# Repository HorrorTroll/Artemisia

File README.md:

# Artemisia
A Pro Micro using ArteryTek AT32F415 MCU

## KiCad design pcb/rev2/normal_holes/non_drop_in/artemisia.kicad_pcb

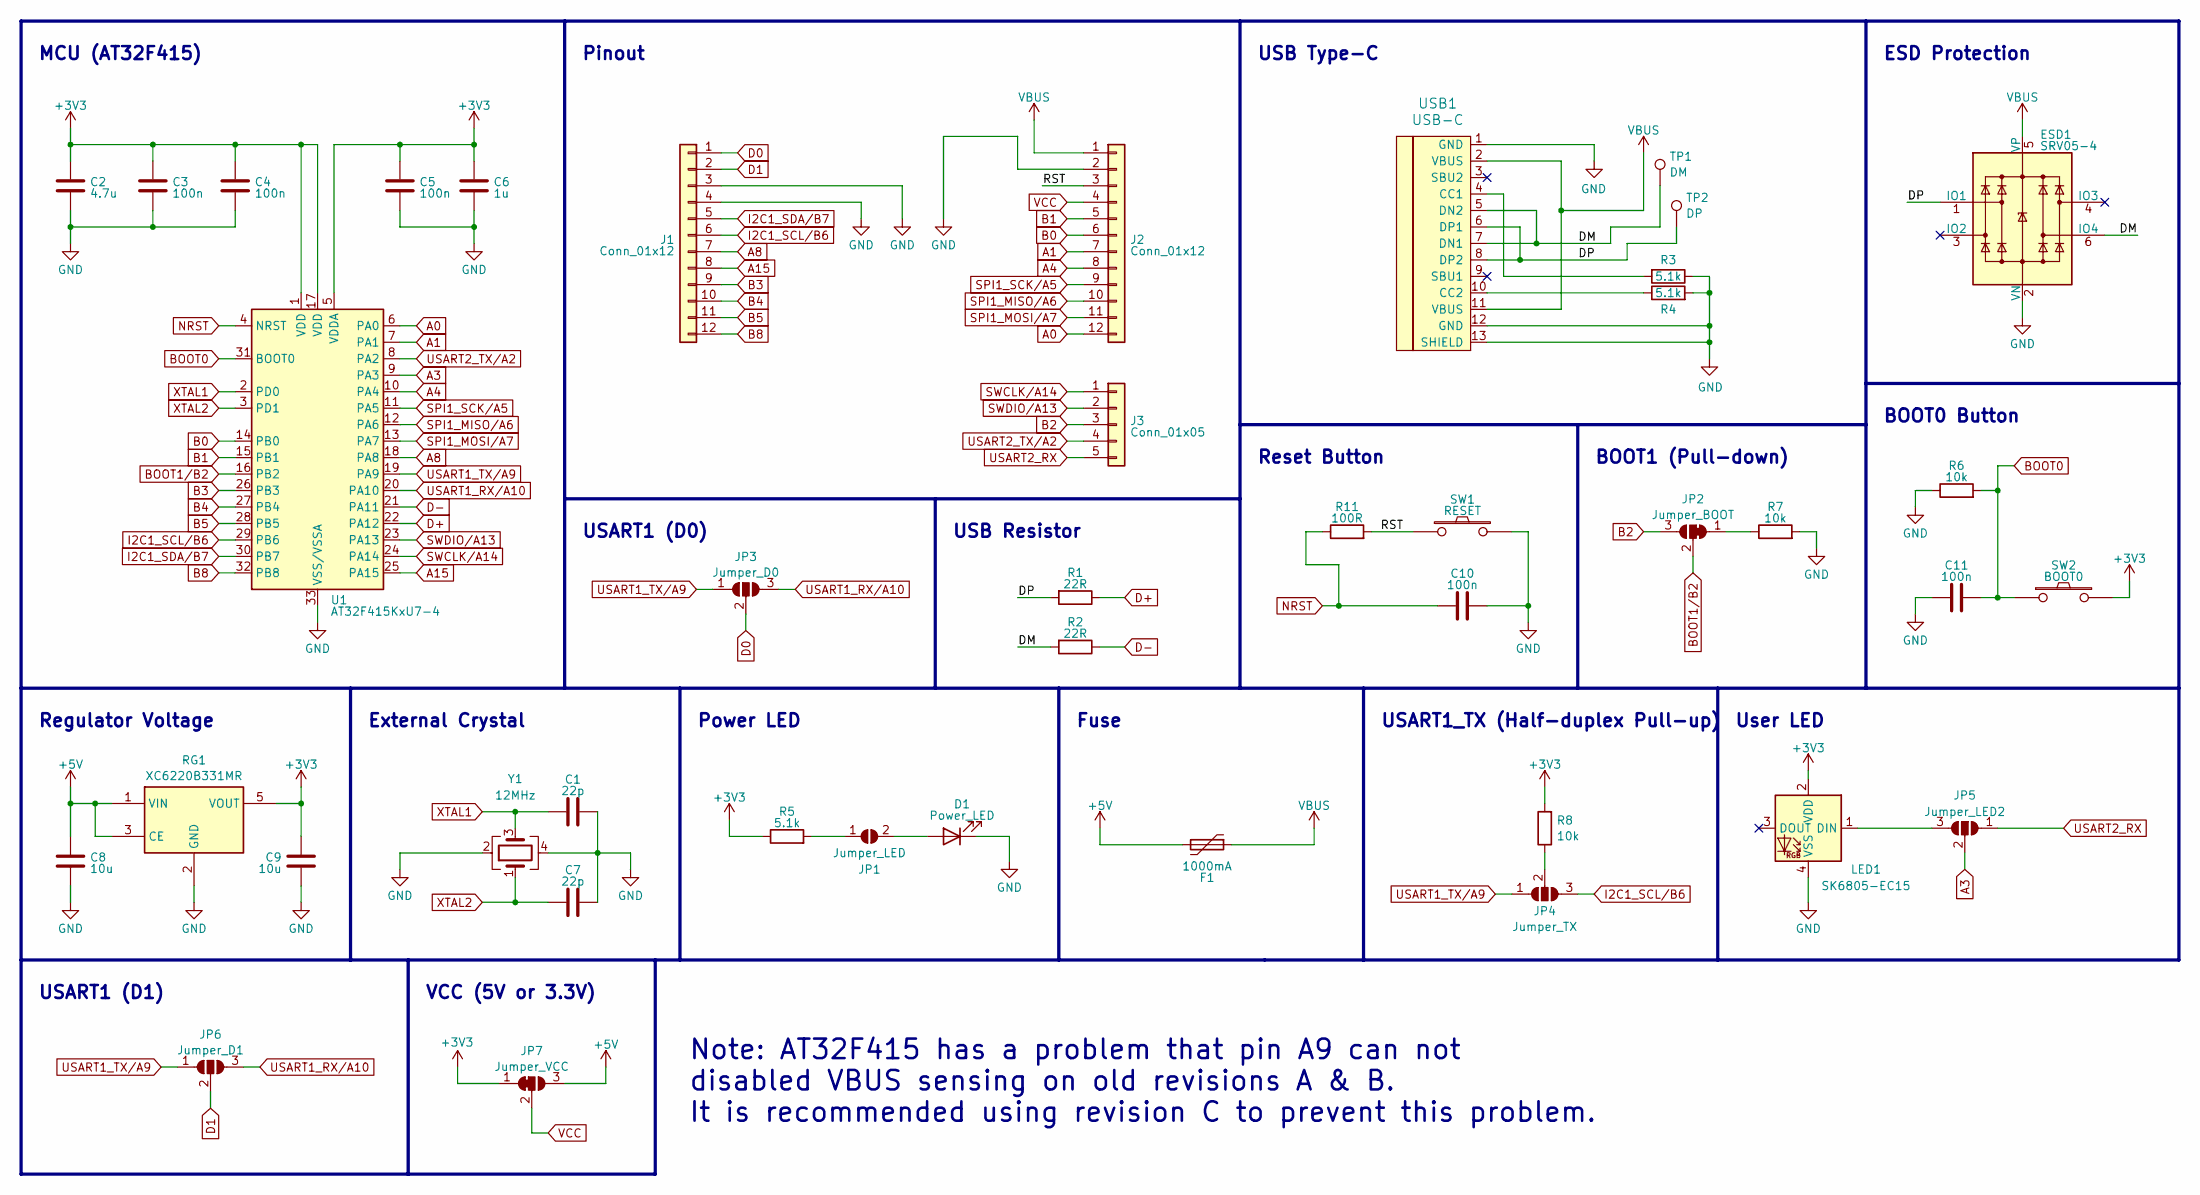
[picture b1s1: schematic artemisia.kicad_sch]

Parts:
C1, C7: 22p; C_0402_1005Metric; LCSC Part Number C1555
C2: 4.7u; C_0402_1005Metric; LCSC Part Number C23733
C3, C4, C5, C10, C11: 100n; C_0402_1005Metric; LCSC Part Number C1525
C6: 1u; C_0402_1005Metric; LCSC Part Number C52923
C8, C9: 10u; C_0402_1005Metric; LCSC Part Number C15525
D1: Power_LED; LED_0402_1005Metric; LCSC Part Number C965794
ESD1: SRV05-4; SOT-23-6; LCSC Part Number C85364
F1: 1000mA; Fuse_0603_1608Metric; LCSC Part Number C516069
J1: Conn_01x12; Pinouts_Holes_01x12_flip
J2: Conn_01x12; Pinouts_Holes_01x12
J3: Conn_01x05; Pinouts_Holes_01x05
JP1: Jumper_LED; SolderJumper-2_Open_Small
JP2: Jumper_BOOT; SolderJumper-3_Bridged_12_Small
JP3: Jumper_D0; SolderJumper-3_Open_Small
JP4: Jumper_TX; SolderJumper-3_Open_Small
JP5: Jumper_LED2; SolderJumper-3_Open_Small
JP6: Jumper_D1; SolderJumper-3_Open_Small
JP7: Jumper_VCC; SolderJumper-3_Bridged_12_Small
LED1: SK6805-EC15; LED_SK6805_EC15_1.5x1.5mm; LCSC Part Number C2890035
R1, R2: 22R; R_0402_1005Metric; LCSC Part Number C25092
R3, R4, R5: 5.1k; R_0402_1005Metric; LCSC Part Number C25905
R6, R7, R8: 10k; R_0402_1005Metric; LCSC Part Number C25744
R11: 100R; R_0402_1005Metric; LCSC Part Number C25076
RG1: XC6220B331MR; SOT-23-5_custom; LCSC Part Number C3040644
SW1: RESET; SW_SPST_Little_Turtle_2P_no_silk; LCSC Part Number C720477
SW2: BOOT0; SW_SPST_Little_Turtle_2P_no_silk_reversible; LCSC Part Number C720477
TP1: DM; TestPoint_Pad_D1.0mm_no_silk
TP2: DP; TestPoint_Pad_D1.0mm_no_silk
U1: AT32F415KxU7-4; QFN-32_4x4mm_ThermalVias; LCSC Part Number C528424
USB1: USB-C; USB-C-C168688; LCSC Part Number C3019717
Y1: 12MHz; Crystal_SMD_3225-4Pin_3.2x2.5mm; LCSC Part Number C9002

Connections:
+3V3: C2.2, C3.2, C4.2, C5.2, C6.2, C9.1, JP7.1 (A), LED1.2 (VDD), R5.1, R8.2, RG1.5 (VOUT), SW2.2, U1.1 (VDD), U1.5 (VDDA), U1.17 (VDD)
+5V: C8.2, F1.2, JP7.3 (B), RG1.1 (VIN), RG1.3 (CE)
/DM: ESD1.6 (IO4), R2.2, TP1.1, USB1.5 (DN2), USB1.7 (DN1)
/DP: ESD1.1 (IO1), R1.2, TP2.1, USB1.6 (DP1), USB1.8 (DP2)
/RST: J2.3, R11.2, SW1.1
A0: J2.12, U1.6 (PA0)
A1: J2.7, U1.7 (PA1)
A3: JP5.2 (C), U1.9 (PA3)
A4: J2.8, U1.10 (PA4)
A8: J1.7, U1.18 (PA8)
A15: J1.8, U1.25 (PA15)
B0: J2.6, U1.14 (PB0)
B1: J2.5, U1.15 (PB1)
B2: J3.3, JP2.3 (B)
B3: J1.9, U1.26 (PB3)
B4: J1.10, U1.27 (PB4)
B5: J1.11, U1.28 (PB5)
B8: J1.12, U1.32 (PB8)
BOOT0: C11.2, R6.2, SW2.1, U1.31 (BOOT0)
BOOT1/B2: JP2.2 (C), U1.16 (PB2)
D0: J1.1, JP3.2 (C)
D1: J1.2, JP6.2 (C)
D+: R1.1, U1.22 (PA12)
D-: R2.1, U1.21 (PA11)
GND: C1.2, C2.1, C3.1, C4.1, C5.1, C6.1, C7.2, C8.1, C9.2, C10.1, C11.1, D1.1 (K), ESD1.2 (VN), J1.3, J1.4, J2.2, LED1.4 (VSS), R3.1, R4.2, R6.1, R7.2, RG1.2 (GND), SW1.2, U1.33 (VSS/VSSA), USB1.1 (GND), USB1.12 (GND), USB1.13 (SHIELD), Y1.2, Y1.4
I2C1_SCL/B6: J1.6, JP4.3 (B), U1.29 (PB6)
I2C1_SDA/B7: J1.5, U1.30 (PB7)
NRST: C10.2, R11.1, U1.4 (NRST)
unnamed: D1.2 (A), JP1.2 (B)
unnamed: JP1.1 (A), R5.2
unnamed: JP2.1 (A), R7.1
unnamed: JP4.2 (C), R8.1
unnamed: JP5.3 (B), LED1.1 (DIN)
unnamed: R3.2, USB1.4 (CC1)
unnamed: R4.1, USB1.10 (CC2)
SPI1_MISO/A6: J2.10, U1.12 (PA6)
SPI1_MOSI/A7: J2.11, U1.13 (PA7)
SPI1_SCK/A5: J2.9, U1.11 (PA5)
SWCLK/A14: J3.1, U1.24 (PA14)
SWDIO/A13: J3.2, U1.23 (PA13)
USART1_RX/A10: JP3.3 (B), JP6.3 (B), U1.20 (PA10)
USART1_TX/A9: JP3.1 (A), JP4.1 (A), JP6.1 (A), U1.19 (PA9)
USART2_RX: J3.5, JP5.1 (A)
USART2_TX/A2: J3.4, U1.8 (PA2)
VBUS: ESD1.5 (VP), F1.1, J2.1, USB1.2 (VBUS), USB1.11 (VBUS)
VCC: J2.4, JP7.2 (C)
XTAL1: C1.1, U1.2 (PD0), Y1.3
XTAL2: C7.1, U1.3 (PD1), Y1.1

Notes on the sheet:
BOOT0 Button
MCU (AT32F415)
USART1 (D0)
USART1 (D1)
Power LED
ESD Protection
Regulator Voltage
VCC (5V or 3.3V)
Note: AT32F415 has a problem that pin A9 can not disabled VBUS sensing on old revisions A & B. It is recommended using revision C to prevent this problem.
User LED
USB Resistor
BOOT1 (Pull-down)
Pinout
External Crystal
USB Type-C
USART1_TX (Half-duplex Pull-up)
Fuse
Reset Button

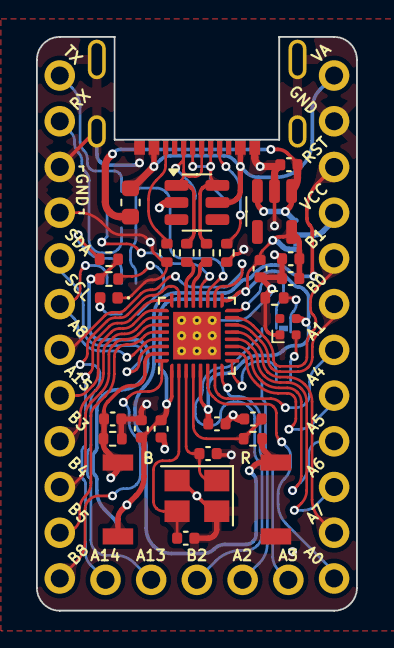
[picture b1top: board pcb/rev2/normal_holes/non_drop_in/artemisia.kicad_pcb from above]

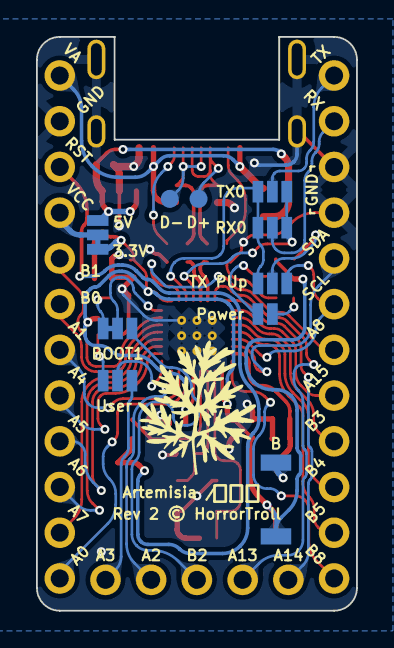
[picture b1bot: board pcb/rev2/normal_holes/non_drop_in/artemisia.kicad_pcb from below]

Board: 2 copper layers, 17.8 x 31.9 mm, 42 parts (10 on the bottom side), 48 nets.

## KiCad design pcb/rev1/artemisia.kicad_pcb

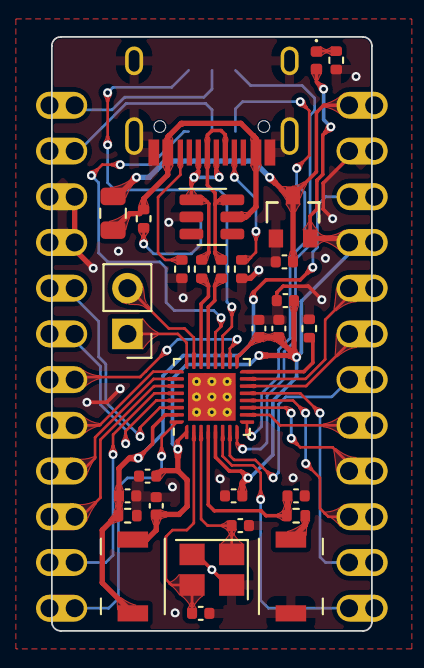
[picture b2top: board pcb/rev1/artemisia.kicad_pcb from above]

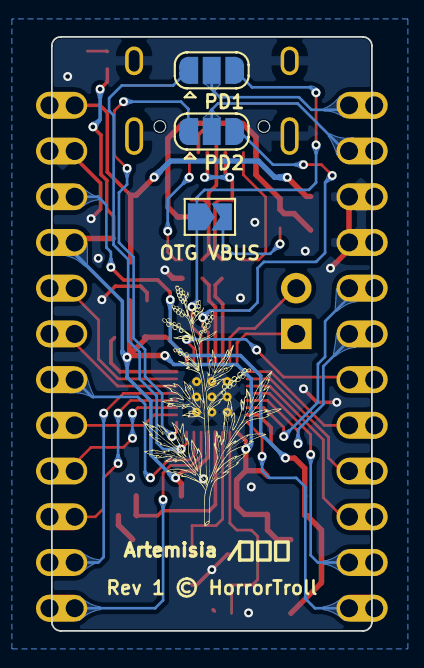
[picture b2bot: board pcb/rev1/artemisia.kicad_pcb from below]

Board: 2 copper layers, 17.8 x 33.0 mm, 35 parts (3 on the bottom side), 42 nets.

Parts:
C1, C7: 22p; C_0402_1005Metric
C2: 4.7u; C_0402_1005Metric
C3, C4, C5, C10, C11: 100n; C_0402_1005Metric
C6, C8, C9: 1u; C_0402_1005Metric
D1: Power LED; LED_0402_1005Metric
ESD1: SRV05-4; SOT-23-6
F1: 500mA; Fuse_0805_2012Metric
J1, J2: Conn_01x12_Male; Pinouts_Castellated_Oval_01x12
J3: Conn_01x02; PinHeader_1x02_P2.54mm_Vertical
JP1, JP2: SolderJumper_3_Bridged12; SolderJumper-3_P1.3mm_Open_RoundedPad1.0x1.5mm
JP3: SolderJumper_2_Open; SolderJumper-2_P1.3mm_Open_TrianglePad1.0x1.5mm
R1, R2: 22R; R_0402_1005Metric
R3, R4: 5.1k; R_0402_1005Metric
R5, R6, R7, R10: 10k; R_0402_1005Metric
R11: 100R; R_0402_1005Metric
RG1: XC6206P332MR
SW1: RESET; SW_SPST_Litte_Turtle_2P
SW2: BOOT0; SW_SPST_Litte_Turtle_2P
U1: AT32F415KxU7-4; AT32F4xx_QFN-32_4x4mm
USB1: HRO-TYPE-C-31-M-12
Y1: 8Mhz; Crystal_SMD_3225-4Pin_3.2x2.5mm

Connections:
+3V3: C2.2, C3.2, C4.2, C5.2, C6.2, C9.1, D1.2 (A), J2.9, RG1.2 (VOUT), SW2.2, U1.1 (VDD), U1.5 (VDDA), U1.17 (VDD)
+5V: C8.1, F1.2, J2.12, RG1.3 (VIN)
/DM: ESD1.6 (IO4), R2.2, USB1.5 (DN2), USB1.7 (DN1)
/DP: ESD1.1 (IO1), R1.2, USB1.6 (DP1), USB1.8 (DP2)
A0: J2.1, U1.6 (PA0)
A1: J2.6, U1.7 (PA1)
A4: J2.5, U1.10 (PA4)
A8: J1.7, U1.18 (PA8)
A15: J1.8, U1.25 (PA15)
B0: J2.7, U1.14 (PB0)
B1: J2.8, U1.15 (PB1)
B3: J1.9, U1.26 (PB3)
B4: J1.10, U1.27 (PB4)
B5: J1.11, U1.28 (PB5)
B8: J1.12, U1.32 (PB8)
BOOT0: C11.2, J2.10, R6.2, SW2.1, U1.31 (BOOT0)
BOOT1: R7.1, U1.16 (PB2)
D+: R1.1, U1.22 (PA12)
D-: R2.1, U1.21 (PA11)
GND: C1.2, C2.1, C3.1, C4.1, C5.1, C6.1, C7.2, C8.2, C9.2, C10.1, C11.1, ESD1.2 (VN), J1.3, J1.4, J2.11, R3.1, R4.2, R5.1, R6.1, R7.2, RG1.1 (VSS), SW1.2, U1.33 (VSS/VSSA), USB1.1 (GND), USB1.12 (GND), USB1.13 (SHIELD), Y1.2, Y1.4
I2C1_SCL/B6: J1.6, U1.29 (PB6)
I2C1_SDA/B7: J1.5, U1.30 (PB7)
NRST: C10.2, R11.1, U1.4 (NRST)
unnamed: D1.1 (K), R5.2
unnamed: R11.2, SW1.1
unnamed: R3.2, USB1.4 (CC1)
unnamed: R4.1, USB1.10 (CC2)
OTGFS_VBUS/A9: JP3.2 (B), R10.1
PD1: J1.1, JP1.2 (C)
PD2: J1.2, JP2.2 (C)
SPI1_MISO/A6: J2.3, U1.12 (PA6)
SPI1_MOSI/A7: J2.2, U1.13 (PA7)
SPI1_SCK/A5: J2.4, U1.11 (PA5)
SWCLK/A14: J3.1, U1.24 (PA14)
SWDIO/A13: J3.2, U1.23 (PA13)
USART1_RX/A10: JP2.3 (B), U1.20 (PA10)
USART1_TX/A9: JP1.3 (B), JP3.1 (A), U1.19 (PA9)
USART2_RX/A3: JP2.1 (A), U1.9 (PA3)
USART2_TX/A2: JP1.1 (A), U1.8 (PA2)
VBUS: ESD1.5 (VP), F1.1, R10.2, USB1.2 (VBUS), USB1.11 (VBUS)
XTAL1: C1.1, U1.2 (PD0), Y1.3
XTAL2: C7.1, U1.3 (PD1), Y1.1

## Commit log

2024-04-25 Added files

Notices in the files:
pcb/rev1/artemisia.kicad_pcb:
Copyright © 2023 HorrorTroll
GPL2 License
Rev 1 © HorrorTroll
pcb/rev2/castellated_holes/drop_in/artemisia.kicad_sch:
Copyright © 2024 HorrorTroll
pcb/rev2/normal_holes/non_drop_in/artemisia.kicad_pcb:
Rev 2 © HorrorTroll
